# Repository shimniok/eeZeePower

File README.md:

# eeZeePower

If you're sick of hunting around for a power source for your breadboard projects and want a simple, small, 
and convenient power module, well, I feel you. Here's the solution. After you solder in the pin headers,
plug in a USB mini-B cable, select 3.3V or 5V, it's time to Make while 
your pals are still trying to figure out how to wire that 9V battery to a 7805.

## Features

* Selectable 3.3V / VUSB (5V) output meets your common prototyping needs
* Maximum current of 500mA
* USB Mini-B input because we all have a gazillion of these cables
* Two sets of output pins for stable installation
* Small; only takes up a tiny corner of the breadboard
* 100uF and 0.1uF filtering capacitors on the output
* 10uF and 0.1uF filtering caps on the regulator input
* All SMT components populated
* Just add pin headers

[Buy now on Tindie](https://www.tindie.com/products/bot_thoughts/eezee-power/)

[Documentation](https://github.com/shimniok/eeZeePower/tree/master/documentation)

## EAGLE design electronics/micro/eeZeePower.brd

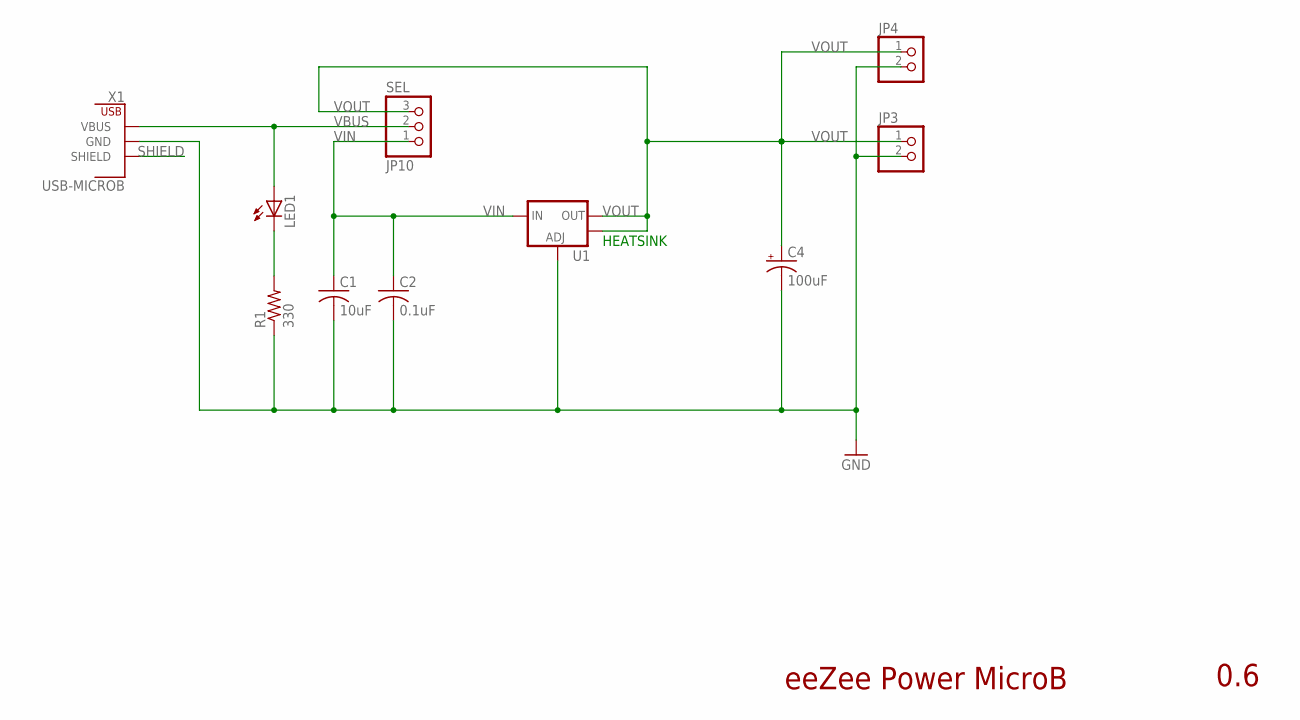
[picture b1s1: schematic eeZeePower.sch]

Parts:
C1: 10uF; C1206
C2: 0.1uF; C0603
C4: 100uF; SMC_B
JP3, JP4: PINHD-1X02_2.54-S; 1X02-S
JP10: SEL; 1X03-S
LED1: LEDCHIPLED_1206; CHIPLED_1206
R1: 330; R0603
U1: V_REG_LM1117SOT223; SOT223
X1: USB-MICROB; USB-MICROB-4

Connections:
GND: C1.2, C2.2, C4.-, JP3.2, JP4.2, R1.1, U1.1 (ADJ), X1.GND
unnamed: LED1.C, R1.2
SHIELD: X1.SHIELD1 (SHIELD), X1.SHIELD2 (SHIELD), X1.SHIELD3 (SHIELD), X1.SHIELD4 (SHIELD), X1.SHIELD5 (SHIELD), X1.SHIELD6 (SHIELD)
VBUS: JP10.2, LED1.A, X1.VBUS
VIN: C1.1, C2.1, JP10.1, U1.3 (IN)
VOUT: C4.+, JP3.1, JP4.1, JP10.3, U1.2 (OUT), U1.4 (OUT)

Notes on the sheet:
eeZee Power MicroB
0.6
HEATSINK

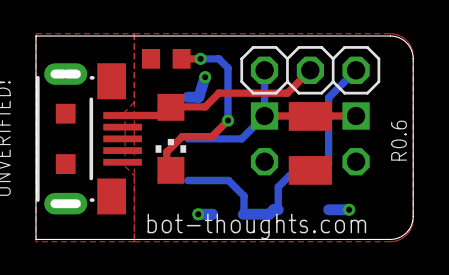
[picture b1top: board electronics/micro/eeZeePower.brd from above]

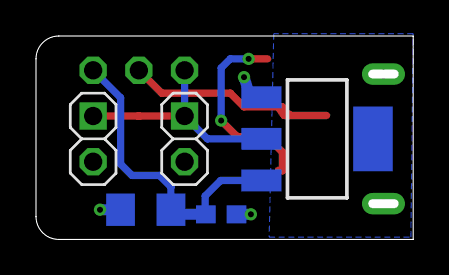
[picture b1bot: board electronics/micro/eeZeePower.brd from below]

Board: 2 copper layers, 21.0 x 11.3 mm, 10 parts (5 on the bottom side), 6 nets.

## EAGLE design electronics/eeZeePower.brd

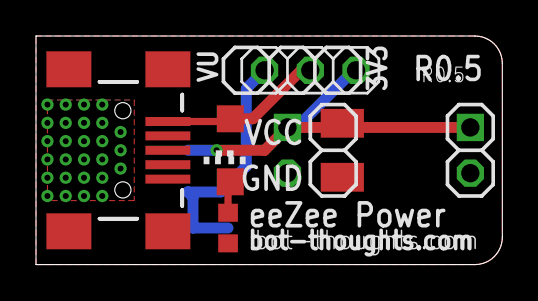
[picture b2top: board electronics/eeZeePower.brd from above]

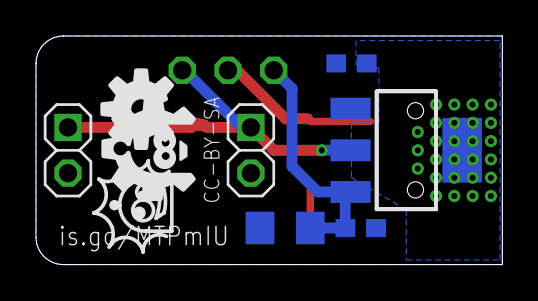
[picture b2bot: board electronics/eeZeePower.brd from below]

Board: 2 copper layers, 25.9 x 12.7 mm, 12 parts (7 on the bottom side), 5 nets.

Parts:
C1: 10uF; C1206
C2, C3: 0.1uF; C0603
C4: 100uF; SMC_B
JP3, JP4: 1X02-S
JP10: SEL; 1X03-S
LED1: CHIPLED_1206
R1: R0603
U1: SOT223
U$1: USB-MINIB-5PIN; USB-MINIB
U$2: BTLOGO-LOGO-MD; BTLOGOM

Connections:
GND: C1.2, C2.2, C3.2, C4.-, JP3.2, JP4.2, R1.1, U1.1, U$1.GND, U$1.MTN1, U$1.MTN2, U$1.MTN3, U$1.MTN4
unnamed: LED1.C, R1.2
VBUS: JP10.2, LED1.A, U$1.VBUS
VIN: C1.1, C2.1, JP10.1, U1.3
VOUT: C3.1, C4.+, JP3.1, JP4.1, JP10.3, U1.2, U1.4

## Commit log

2013-01-08 Initial revision
2013-01-08 Changed view
2013-01-29 Fixed jumper labels
2013-06-14 Renamed to remove space
2013-08-06 Rev 0.3 converted to standard 1206 LED, centered components, mitered corners, moved some components around, removed component names.
2014-05-15 Converted to standard 1206 10uF, placed input bypass caps on bottom. Rearranged silk, centered pin headers.
2014-05-15 Revised silk, placed input filter caps on bottom, switch 10uF to standard 1206 package, centered pin headers.
2014-10-17 Changed to 10mil/8mil spacing, improved thermal design, connected heatsink to VOUT.
2014-10-17 Updated version #
2022-03-23 updated main readme
2022-03-23 added mu-B indicator on silk
2022-03-23 microb: Updated version to 0.6
2022-03-23 updated microb gerbers
2022-03-23 microb: moved silkscreen
2022-03-23 Converted documentation to markdown, created full user guide
2022-03-23 moved electronics into subdirectory
2022-03-23 Revised silk, updated gerbers
2022-03-23 Updated version # in schematic
2022-03-23 Fix labels for voltage select jumper
2022-03-23 added gitignore
2022-03-23 initial USB micro-B version
2022-03-23 minib: updated gerbers, zip
2022-03-23 moved minib files into mini folder
2022-03-23 added assembly guide
2022-03-23 microb: updated zip, gerbers
2022-03-23 microb: added value to LED resistor, removed silk value
2022-03-23 microb: updated silk, updated board name to micro b in schematic
2022-03-23 updated microb zip
2022-03-23 updated specs
2022-03-23 added images to user guide
2022-03-23 updated microb after fixing silk in package
2022-03-23 minib: replaced logo; moved power select headers, passives; added help url; updated gerbers, zip
2022-03-23 Change LED to standard 1206, centered and moved components, mitered corners, removed component names.
2022-03-23 Changed permissions on electronics files
2022-03-23 Create README.md in main directory
2022-03-23 updated microb with new four-pad library version, added shielding to ground, fixed missing junction
2022-03-23 usbc initial version
2022-03-24 c: added help url to board, silk layout tweaks
2022-03-24 added drawings for micro usb connectors
2022-03-24 added drawing for usb c connector
2022-03-25 microb: replaced usb micro b connector symbol & footprint
2022-03-25 layout tweak, shrink board width, fix gnd pour connection

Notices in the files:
electronics/eeZeePower.brd:
CC-BY-SA
parts and their libraries:
SparkFun: Licensing: CC v3.0 Share-Alike You are welcome to use this library for commercial purposes.
